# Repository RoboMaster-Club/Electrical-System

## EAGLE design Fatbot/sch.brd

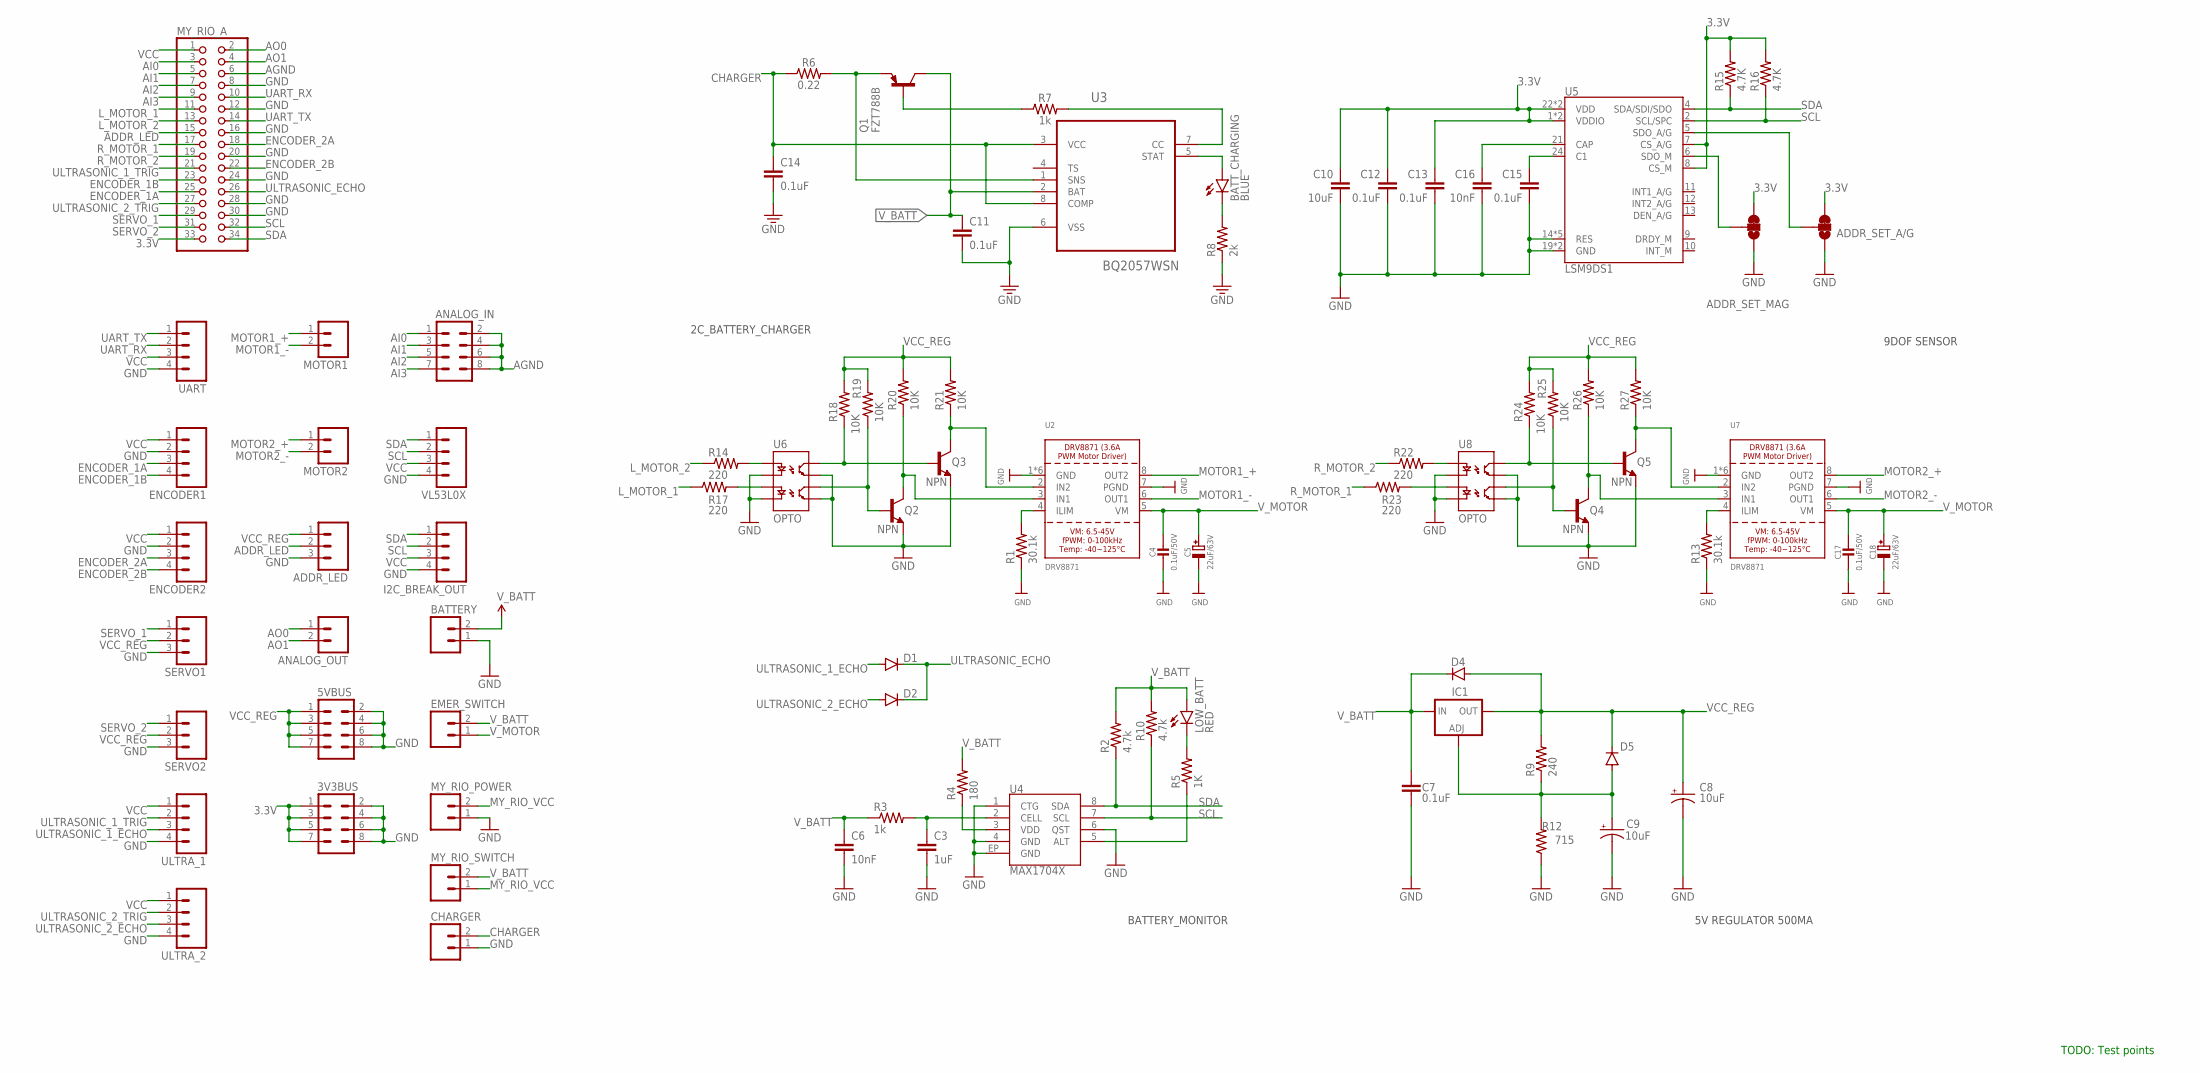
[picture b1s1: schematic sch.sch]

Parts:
3V3BUS, 5VBUS: M04X2; 2X4
ADDR_LED: M03POLAR; MOLEX-1X3
ADDR_SET_A/G: JUMPER-PAD-3-2OF3_NC_BY_TRACE_SMALL; PAD-JUMPER-3-2OF3_NC_BY_TRACE_YES_SILK_FULL_BOX
ADDR_SET_MAG: JUMPER-PAD-3-2OF3_NC_BY_TRACE_SMALL; PAD-JUMPER-3-2OF3_NC_BY_TRACE_YES_SILK_FULL_BOX
ANALOG_IN: M04X2; 2X4
ANALOG_OUT: M021X02_NO_SILK; 1X02_NO_SILK@1
BATTERY: CONN_02; 1X02
BATT_CHARGING: BLUE; LED-0603
C3: 1uF; 0402-CAP
C4, C17: 0.1uF/50V; 0805-NO
C5, C18: 22uF/63V; PANASONIC_D
C6: 10nF; 0402-CAP
C7, C12, C13, C15: 0.1uF; 0603-CAP
C8, C9: 10uF; EIA3216
C10: 10uF; 0603-CAP
C11, C14: 0.1uF; 0603
C16: 10nF; 0603-CAP
CHARGER: CONN_02; 1X02
D1, D2: DIODESOD123; SOD-123
D4, D5: 1N4002; SOD-123
EMER_SWITCH: CONN_02; 1X02
ENCODER1, ENCODER2: M041X04_NO_SILK; 1X04_NO_SILK
I2C_BREAK_OUT: M041X04_NO_SILK; 1X04_NO_SILK
IC1: LM317MBSTT3; SOT223; PARTNUMBER LM317M
LOW_BATT: RED; LED-0603
MOTOR1, MOTOR2: M02PTH; 1X02@1
MY_RIO_A: PINHD-2X17; 2X17
MY_RIO_POWER: CONN_02; 1X02
MY_RIO_SWITCH: CONN_02; 1X02
Q1: FZT788B; SOT230P700X180-4N
Q2, Q3, Q4, Q5: NPN; SOT23-3
R1, R13: 30.1k; 0603-RES
R2, R10: 4.7k; 0402-RES
R3: 1k; 0402-RES
R4: 180; 0402-RES
R5: 1K; 0603-RES
R6: 0.22; 0805@1
R7: 1k; 0603
R8: 2k; 0603-RES
R9: 240; 0603-RES
R12: 715; 0603-RES
R14, R17, R22, R23: 220; 0603-RES
R15, R16: 4.7K; 0603-RES
R18, R19, R20, R21, R24, R25, R26, R27: 10K; 0603-RES
SERVO1, SERVO2: M03POLAR; MOLEX-1X3
U2, U7: DRV8871; HSOP8
U3: BQ2057WSN; SOIC127P600X175-8N
U4: MAX1704X; TDFN-8
U5: LSM9DS1; LGA24-8X4
U6, U8: OPTO; SO08-2
UART: M04NO_SILK_ALL_ROUND; 1X04_NO_SILK_ALL_ROUND
ULTRA_1, ULTRA_2: M041X04_NO_SILK; 1X04_NO_SILK
VL53L0X: M041X04_NO_SILK; 1X04_NO_SILK

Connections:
3.3V: 3V3BUS.1, 3V3BUS.3, 3V3BUS.5, 3V3BUS.7, ADDR_SET_A/G.3, ADDR_SET_MAG.3, C10.1, C12.1, C13.1, MY_RIO_A.33, R15.2, R16.2, U5.1 (VDDIO), U5.3 (VDDIO), U5.7 (CS_A/G), U5.8 (CS_M), U5.22 (VDD), U5.23 (VDD)
ADDR_LED: ADDR_LED.2, MY_RIO_A.15
AGND: ANALOG_IN.2, ANALOG_IN.4, ANALOG_IN.6, ANALOG_IN.8, MY_RIO_A.6
AI0: ANALOG_IN.1, MY_RIO_A.3
AI1: ANALOG_IN.3, MY_RIO_A.5
AI2: ANALOG_IN.5, MY_RIO_A.7
AI3: ANALOG_IN.7, MY_RIO_A.9
ALT: R5.1, U4.5 (ALT)
AO0: ANALOG_OUT.1, MY_RIO_A.2
AO1: ANALOG_OUT.2, MY_RIO_A.4
BATTERY_MONITOR_2: BATT_CHARGING.A, U3.5 (STAT)
CHARGER: C14.1, CHARGER.2, R6.1, U3.3 (VCC), U3.8 (COMP)
ENCODER_1A: ENCODER1.3, MY_RIO_A.25
ENCODER_1B: ENCODER1.4, MY_RIO_A.23
ENCODER_2A: ENCODER2.3, MY_RIO_A.18
ENCODER_2B: ENCODER2.4, MY_RIO_A.22
GND: 3V3BUS.2, 3V3BUS.4, 3V3BUS.6, 3V3BUS.8, 5VBUS.2, 5VBUS.4, 5VBUS.6, 5VBUS.8, ADDR_LED.3, ADDR_SET_A/G.1, ADDR_SET_MAG.1, BATTERY.1, C3.2, C4.2, C5.-, C6.2, C7.2, C8.C (-), C9.C (-), C10.2, C11.2, C12.2, C13.2, C14.2, C15.2, C16.2, C17.2, C18.-, CHARGER.1, ENCODER1.2, ENCODER2.2, I2C_BREAK_OUT.4, MY_RIO_A.8, MY_RIO_A.12, MY_RIO_A.16, MY_RIO_A.20, MY_RIO_A.24, MY_RIO_A.28, MY_RIO_A.30, MY_RIO_POWER.1, Q2.2 (E), Q3.2 (E), Q4.2 (E), Q5.2 (E), R1.1, R8.1, R12.1, R13.1, SERVO1.3, SERVO2.3, U2.1 (GND), U2.7 (PGND), U2.GND, U2.P$1 (GND), U2.P$2 (GND), U2.P$3 (GND), U2.P$4 (GND), U3.6 (VSS), U4.1 (CTG), U4.4 (GND), U4.6 (QST), U4.EP (GND), U5.14 (RES), U5.15 (RES), U5.16 (RES), U5.17 (RES), U5.18 (RES), U5.19 (GND), U5.20 (GND), U6.2 (C1), U6.4 (C2), U6.5 (EM2), U6.7 (EM1), U7.1 (GND), U7.7 (PGND), U7.GND, U7.P$1 (GND), U7.P$2 (GND), U7.P$3 (GND), U7.P$4 (GND), U8.2 (C1), U8.4 (C2), U8.5 (EM2), U8.7 (EM1), UART.4, ULTRA_1.4, ULTRA_2.4, VL53L0X.4
L_MOTOR_1: MY_RIO_A.11, R17.1
L_MOTOR_2: MY_RIO_A.13, R14.1
MOTOR1_+: MOTOR1.1, U2.8 (OUT2)
MOTOR1_-: MOTOR1.2, U2.6 (OUT1)
MOTOR2_+: MOTOR2.1, U7.8 (OUT2)
MOTOR2_-: MOTOR2.2, U7.6 (OUT1)
MY_RIO_VCC: MY_RIO_POWER.2, MY_RIO_SWITCH.1
unnamed: R1.2, U2.4 (ILIM)
unnamed: R17.2, U6.3 (A2)
unnamed: C3.1, R3.2, U4.2 (CELL)
unnamed: R14.2, U6.1 (A1)
unnamed: LOW_BATT.C, R5.2
unnamed: C9.A (+), D5.A, IC1.1 (ADJ), R9.1, R12.2
unnamed: R13.2, U7.4 (ILIM)
unnamed: C16.1, U5.21 (CAP)
unnamed: C15.1, U5.24 (C1)
unnamed: R22.2, U8.1 (A1)
unnamed: R23.2, U8.3 (A2)
unnamed: Q1.3 (E), R6.2, U3.1 (SNS)
unnamed: Q1.1 (B), R7.1
unnamed: R7.2, U3.7 (CC)
unnamed: BATT_CHARGING.C, R8.2
OUT1: Q3.3 (C), R21.1, U2.2 (IN2)
OUT1N: Q3.1 (B), R18.1, U6.8 (CL1)
OUT1N1: Q5.1 (B), R24.1, U8.8 (CL1)
OUT2: Q2.3 (C), R20.1, U2.3 (IN1)
OUT2N: Q2.1 (B), R19.1, U6.6 (CL2)
OUT2N1: Q4.1 (B), R25.1, U8.6 (CL2)
OUT3: Q5.3 (C), R27.1, U7.2 (IN2)
OUT4: Q4.3 (C), R26.1, U7.3 (IN1)
R_MOTOR_1: MY_RIO_A.17, R23.1
R_MOTOR_2: MY_RIO_A.19, R22.1
SCL: I2C_BREAK_OUT.2, MY_RIO_A.32, R10.1, R16.1, U4.7 (SCL), U5.2 (SCL/SPC), VL53L0X.2
SDA: I2C_BREAK_OUT.1, MY_RIO_A.34, R2.1, R15.1, U4.8 (SDA), U5.4 (SDA/SDI/SDO), VL53L0X.1
SDO_A/G: ADDR_SET_A/G.2, U5.5 (SDO_A/G)
SDO_M: ADDR_SET_MAG.2, U5.6 (SDO_M)
SERVO_1: MY_RIO_A.29, SERVO1.1
SERVO_2: MY_RIO_A.31, SERVO2.1
UART_RX: MY_RIO_A.10, UART.2
UART_TX: MY_RIO_A.14, UART.1
ULTRASONIC_1_ECHO: D1.A, ULTRA_1.3
ULTRASONIC_1_TRIG: MY_RIO_A.21, ULTRA_1.2
ULTRASONIC_2_ECHO: D2.A, ULTRA_2.3
ULTRASONIC_2_TRIG: MY_RIO_A.27, ULTRA_2.2
ULTRASONIC_ECHO: D1.C, D2.C, MY_RIO_A.26
VCC: ENCODER1.1, ENCODER2.1, I2C_BREAK_OUT.3, MY_RIO_A.1, UART.3, ULTRA_1.1, ULTRA_2.1, VL53L0X.3
VCC_REG: 5VBUS.1, 5VBUS.3, 5VBUS.5, 5VBUS.7, ADDR_LED.1, C8.A (+), D4.A, D5.C, IC1.4 (OUT), R9.2, R18.2, R19.2, R20.2, R21.2, R24.2, R25.2, R26.2, R27.2, SERVO1.2, SERVO2.2
VDD: R4.1, U4.3 (VDD)
V_BATT: BATTERY.2, C6.1, C7.1, C11.1, D4.C, EMER_SWITCH.2, IC1.3 (IN), LOW_BATT.A, MY_RIO_SWITCH.2, Q1.2 (C), Q1.4 (C), R2.2, R3.1, R4.2, R10.2, U3.2 (BAT)
V_MOTOR: C4.1, C5.+, C17.1, C18.+, EMER_SWITCH.1, U2.5 (VM), U7.5 (VM)

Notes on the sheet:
BATTERY_MONITOR
5V REGULATOR 500MA
9DOF SENSOR
2C_BATTERY_CHARGER
TODO: Test points

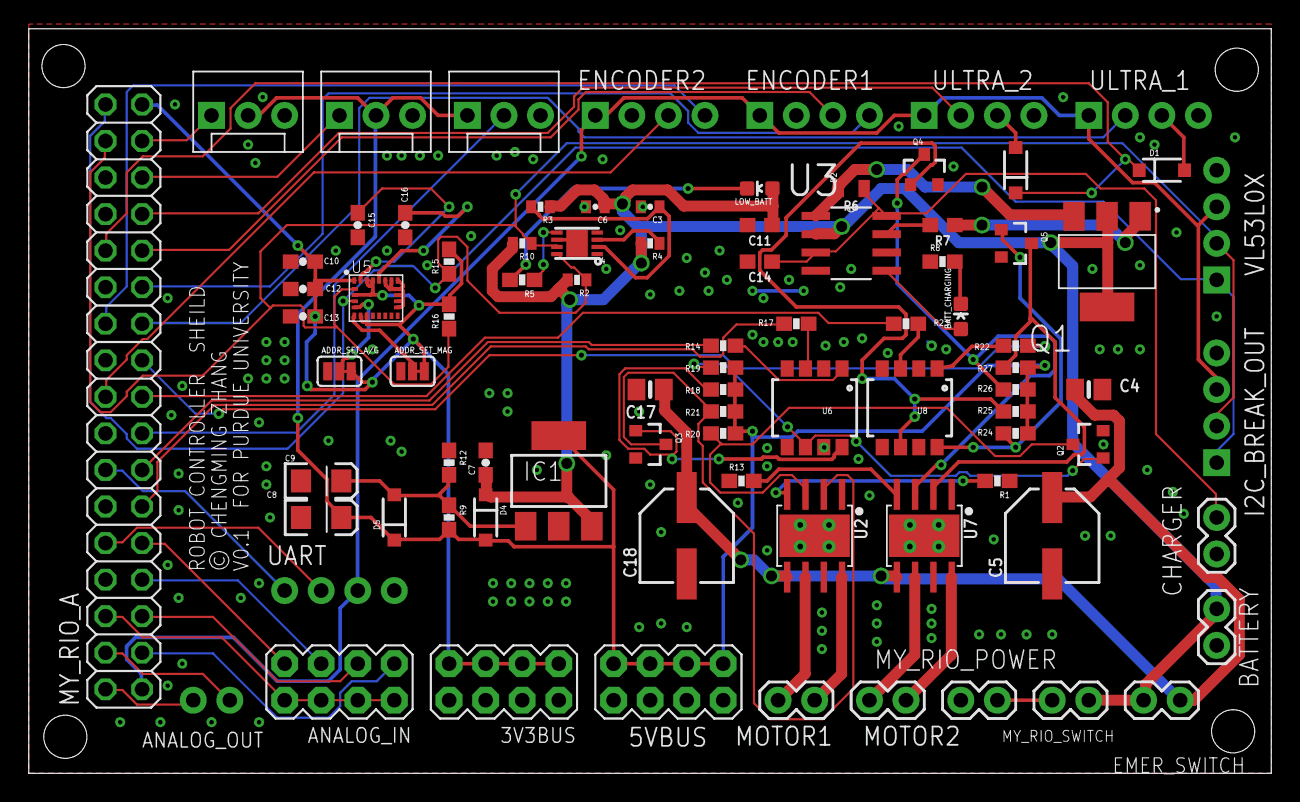
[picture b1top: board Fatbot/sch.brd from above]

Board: 2 copper layers, 86.3 x 51.7 mm, 85 parts (0 on the bottom side), 67 nets.

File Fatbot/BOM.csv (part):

"Part";"Value";"Device";"Package";"Description";"AVAILABILITY";"DESCRIPTION";"MF";"MP";"MPN";"OC_NEWARK";"PACKAGE";"PARTNUMBER";"PRICE";"PROD_ID";"VALUE";
"3V3BUS";"";"M04X2";"2X4";".1" header, two rows of four.";"";"";"";"";"";"";"";"";"";"";"";
"5VBUS";"";"M04X2";"2X4";".1" header, two rows of four.";"";"";"";"";"";"";"";"";"";"";"";
"ADDR_LED";"";"M03POLAR";"MOLEX-1X3";"Header 3";"";"";"";"";"";"";"";"";"";"";"";
"ADDR_SET_A/G";"";"JUMPER-PAD-3-2OF3_NC_BY_TRACE_SMALL";"PAD-JUMPER-3-2OF3_NC_BY_TRACE_YES_SILK_FULL_BOX";"";"";"";"";"";"";"";"";"";"";"";"";
"ADDR_SET_MAG";"";"JUMPER-PAD-3-2OF3_NC_BY_TRACE_SMALL";"PAD-JUMPER-3-2OF3_NC_BY_TRACE_YES_SILK_FULL_BOX";"";"";"";"";"";"";"";"";"";"";"";"";
"ANALOG_IN";"";"M04X2";"2X4";".1" header, two rows of four.";"";"";"";"";"";"";"";"";"";"";"";
"ANALOG_OUT";"";"M021X02_NO_SILK";"1X02_NO_SILK@1";"Standard 2-pin 0.1" header. Use with";"";"";"";"";"";"";"";"";"";"";"";
"BATTERY";"";"CONN_02";"1X02";"Multi connection point. Often used as Generic Header-pin footprint for 0.1 inch spaced/style header connections";"";"";"";"";"";"";"";"";"";"";"";
"BATT_CHARGING";"BLUE";"LED-BLUE0603";"LED-0603";"Blue LEDs for production use";"";"";"";"";"";"unknown";"";"";"";"DIO-08575";"BLUE";
"C3";"1uF";"CAP0402-CAP";"0402-CAP";"Capacitor";"";"";"";"";"";"";"";"";"";"";"";
"C4";"0.1uF/50V";"CAP_CERAMIC0805-NOOUTLINE";"0805-NO";"Ceramic Capacitors";"";"";"";"";"";"";"";"";"";"";"";
"C5";"22uF/63V";"CAP_ELECTROLYTICPANASONIC_D";"PANASONIC_D";"Electrolytic Capacitors";"";"";"";"";"";"";"";"";"";"";"";
"C6";"10nF";"CAP0402-CAP";"0402-CAP";"Capacitor";"";"";"";"";"";"";"";"";"";"";"";
"C7";"0.1uF";"0.1UF-25V(+80/-20%)(0603)";"0603-CAP";"CAP-00810";"";"";"";"";"";"";"";"";"";"CAP-00810";"0.1uF";
"C8";"10uF";"10UF-16V-10%(TANT)";"EIA3216";"CAP-00811";"";"";"";"";"";"";"";"";"";"CAP-00811";"10uF";
"C9";"10uF";"10UF-16V-10%(TANT)";"EIA3216";"CAP-00811";"";"";"";"";"";"";"";"";"";"CAP-00811";"10uF";
"C10";"10uF";"10UF-6.3V-20%(0603)";"0603-CAP";"CAP-11015";"";"";"";"";"";"";"";"";"";"CAP-11015";"10uF";
"C11";"0.1uF";"0.1UF-0603-25V-(+80/-20%)";"0603";"0.1µF ceramic capacitors";"";"";"";"";"";"unknown";"";"";"";"CAP-00810";"0.1uF";
"C12";"0.1uF";"0.1UF-25V(+80/-20%)(0603)";"0603-CAP";"CAP-00810";"";"";"";"";"";"";"";"";"";"CAP-00810";"0.1uF";
"C13";"0.1uF";"0.1UF-25V(+80/-20%)(0603)";"0603-CAP";"CAP-00810";"";"";"";"";"";"";"";"";"";"CAP-00810";"0.1uF";
"C14";"0.1uF";"0.1UF-0603-25V-(+80/-20%)";"0603";"0.1µF ceramic capacitors";"";"";"";"";"";"unknown";"";"";"";"CAP-00810";"0.1uF";
"C15";"0.1uF";"0.1UF-25V(+80/-20%)(0603)";"0603-CAP";"CAP-00810";"";"";"";"";"";"";"";"";"";"CAP-00810";"0.1uF";
"C16";"10nF";"10NF/10000PF-50V-10%(0603)";"0603-CAP";"CAP-00867";"";"";"";"";"";"";"";"";"";"CAP-00867";"10nF";
"C17";"0.1uF/50V";"CAP_CERAMIC0805-NOOUTLINE";"0805-NO";"Ceramic Capacitors";"";"";"";"";"";"";"";"";"";"";"";
"C18";"22uF/63V";"CAP_ELECTROLYTICPANASONIC_D";"PANASONIC_D";"Electrolytic Capacitors";"";"";"";"";"";"";"";"";"";"";"";
"CHARGER";"";"CONN_02";"1X02";"Multi connection point. Often used as Generic Header-pin footprint for 0.1 inch spaced/style header connections";"";"";"";"";"";"";"";"";"";"";"";
"D1";"";"DIODESOD123";"SOD-123";"Diode";"";"";"";"";"";"";"";"";"";"";"";
"D2";"";"DIODESOD123";"SOD-123";"Diode";"";"";"";"";"";"";"";"";"";"";"";
"D4";"1N4002";"DIODESOD123";"SOD-123";"Diode";"";"";"";"";"";"";"";"";"";"";"";
"D5";"1N4002";"DIODESOD123";"SOD-123";"Diode";"";"";"";"";"";"";"";"";"";"";"";
"EMER_SWITCH";"";"CONN_02";"1X02";"Multi connection point. Often used as Generic Header-pin footprint for 0.1 inch spaced/style header connections";"";"";"";"";"";"";"";"";"";"";"";
"ENCODER1";"";"M041X04_NO_SILK";"1X04_NO_SILK";"Header 4";"";"";"";"";"";"";"";"";"";"";"";
"ENCODER2";"";"M041X04_NO_SILK";"1X04_NO_SILK";"Header 4";"";"";"";"";"";"";"";"";"";"";"";
"I2C_BREAK_OUT";"";"M041X04_NO_SILK";"1X04_NO_SILK";"Header 4";"";"";"";"";"";"";"";"";"";"";"";
"IC1";"LM317MBSTT3";"LM317MBSTT3";"SOT223";"500 mA Adjustable Output Positive Voltage Regulator";"";"";"";"";"";"";"";"LM317M";"";"";"";
"LOW_BATT";"RED";"LED-RED0603";"LED-0603";"Assorted Red LEDs";"";"";"";"";"";"";"";"";"";"DIO-00819";"RED";
"MOTOR1";"";"M02PTH";"1X02@1";"Standard 2-pin 0.1" header. Use with";"";"";"";"";"";"";"";"";"";"";"";
"MOTOR2";"";"M02PTH";"1X02@1";"Standard 2-pin 0.1" header. Use with";"";"";"";"";"";"";"";"";"";"";"";
"MY_RIO_A";"";"PINHD-2X17";"2X17";"PIN HEADER";"";"";"";"";"";"";"";"";"";"";"";
"MY_RIO_POWER";"";"CONN_02";"1X02";"Multi connection point. Often used as Generic Header-pin footprint for 0.1 inch spaced/style header connections";"";"";"";"";"";"";"";"";"";"";"";
"MY_RIO_SWITCH";"";"CONN_02";"1X02";"Multi connection point. Often used as Generic Header-pin footprint for 0.1 inch spaced/style header connections";"";"";"";"";"";"";"";"";"";"";"";
"Q1";"FZT788B";"FZT788B";"SOT230P700X180-4N";"";"";"";"";"";"";"unknown";"";"";"";"";"";
"Q2";"NPN";"TRANSISTOR_NPNSOT23-3";"SOT23-3";"Transistor NPN";"";"";"";"";"";"";"";"";"";"";"";
"Q3";"NPN";"TRANSISTOR_NPNSOT23-3";"SOT23-3";"Transistor NPN";"";"";"";"";"";"";"";"";"";"";"";
"Q4";"NPN";"TRANSISTOR_NPNSOT23-3";"SOT23-3";"Transistor NPN";"";"";"";"";"";"";"";"";"";"";"";
"Q5";"NPN";"TRANSISTOR_NPNSOT23-3";"SOT23-3";"Transistor NPN";"";"";"";"";"";"";"";"";"";"";"";
"R1";"30.1k";"30.1KOHM1/10W1%(0603)";"0603-RES";"RES-08595";"";"";"";"";"";"";"";"";"";"RES-08595";"30.1k";
"R2";"4.7k";"RESISTOR0402-RES";"0402-RES";"Resistor";"";"";"";"";"";"";"";"";"";"";"";
"R3";"1k";"RESISTOR0402-RES";"0402-RES";"Resistor";"";"";"";"";"";"";"";"";"";"";"";
"R4";"180";"RESISTOR0402-RES";"0402-RES";"Resistor";"";"";"";"";"";"";"";"";"";"";"";
"R5";"1K";"1KOHM-1/10W-1%(0603)";"0603-RES";"RES-07856";"";"";"";"";"";"";"";"";"";"RES-07856";"1K";
"R6";"0.22";"0.22OHM-0805-1/4W-1%";"0805@1";"0.22Ω resistor";"";"";"";"";"";"unknown";"";"";"";"RES-09883";"0.22";
"R7";"1k";"1KOHM-0603-1/10W-1%";"0603";"1kΩ resistor";"";"";"";"";"";"unknown";"";"";"";"RES-07856";"1k";
"R8";"2k";"RESISTOR0603";"0603-RES";"Resistor";"";"";"";"";"";"unknown";"";"";"";"";"";
"R9";"240";"240OHM1/10W1%(0603)";"0603-RES";"RES-07849";"";"";"";"";"";"";"";"";"";"RES-07849";"240";
"R10";"4.7k";"RESISTOR0402-RES";"0402-RES";"Resistor";"";"";"";"";"";"";"";"";"";"";"";
"R12";"715";"715OHM1/10W1%(0603)";"0603-RES";"RES-07850";"";"";"";"";"";"";"";"";"";"RES-07850";"715";
"R13";"30.1k";"30.1KOHM1/10W1%(0603)";"0603-RES";"RES-08595";"";"";"";"";"";"";"";"";"";"RES-08595";"30.1k";
"R14";"220";"220OHM-1/10W-1%(0603)";"0603-RES";"RES-07861";"";"";"";"";"";"";"";"";"";"RES-07861";"220";
"R15";"4.7K";"4.7KOHM-1/10W-1%(0603)";"0603-RES";"RES-07857";"";"";"";"";"";"";"";"";"";"RES-07857";"4.7K";
"R16";"4.7K";"4.7KOHM-1/10W-1%(0603)";"0603-RES";"RES-07857";"";"";"";"";"";"";"";"";"";"RES-07857";"4.7K";
"R17";"220";"220OHM-1/10W-1%(0603)";"0603-RES";"RES-07861";"";"";"";"";"";"";"";"";"";"RES-07861";"220";
"R18";"10K";"10KOHM-1/10W-1%(0603)0603";"0603-RES";"RES-00824";"";"";"";"";"";"";"";"";"";"RES-00824";"10K";
"R19";"10K";"10KOHM-1/10W-1%(0603)0603";"0603-RES";"RES-00824";"";"";"";"";"";"";"";"";"";"RES-00824";"10K";
"R20";"10K";"10KOHM-1/10W-1%(0603)0603";"0603-RES";"RES-00824";"";"";"";"";"";"";"";"";"";"RES-00824";"10K";
"R21";"10K";"10KOHM-1/10W-1%(0603)0603";"0603-RES";"RES-00824";"";"";"";"";"";"";"";"";"";"RES-00824";"10K";
"R22";"220";"220OHM-1/10W-1%(0603)";"0603-RES";"RES-07861";"";"";"";"";"";"";"";"";"";"RES-07861";"220";
"R23";"220";"220OHM-1/10W-1%(0603)";"0603-RES";"RES-07861";"";"";"";"";"";"";"";"";"";"RES-07861";"220";
"R24";"10K";"10KOHM-1/10W-1%(0603)0603";"0603-RES";"RES-00824";"";"";"";"";"";"";"";"";"";"RES-00824";"10K";
"R25";"10K";"10KOHM-1/10W-1%(0603)0603";"0603-RES";"RES-00824";"";"";"";"";"";"";"";"";"";"RES-00824";"10K";
"R26";"10K";"10KOHM-1/10W-1%(0603)0603";"0603-RES";"RES-00824";"";"";"";"";"";"";"";"";"";"RES-00824";"10K";
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
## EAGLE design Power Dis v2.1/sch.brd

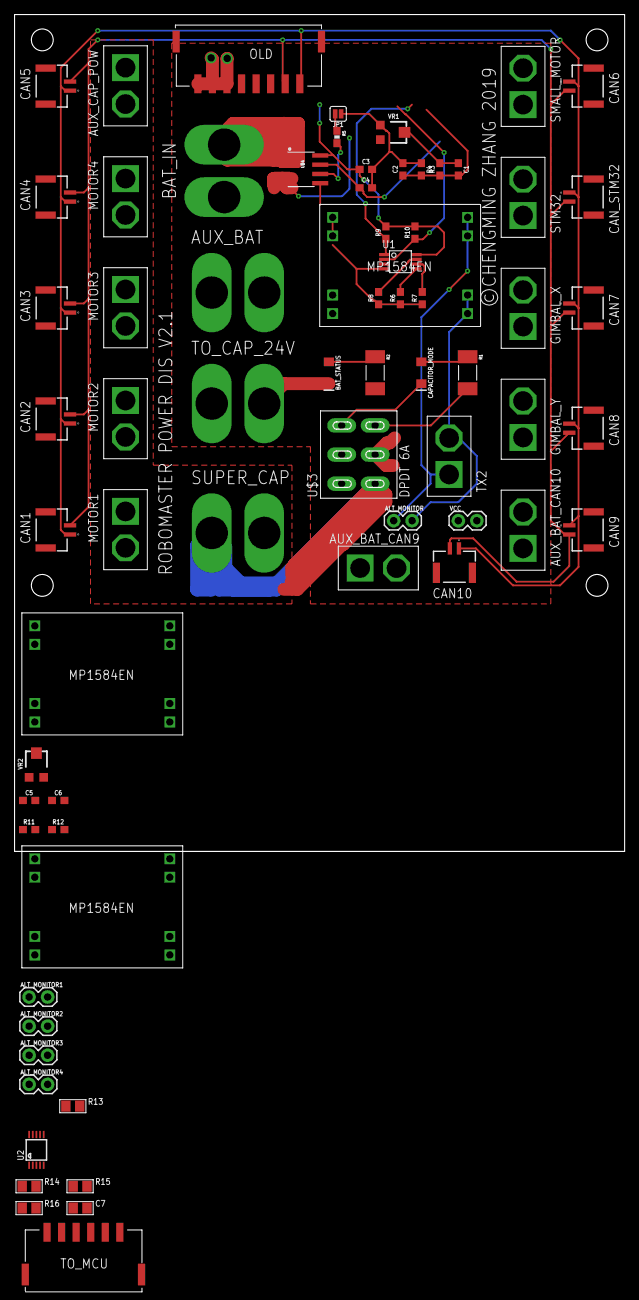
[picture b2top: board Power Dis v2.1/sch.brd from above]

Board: 2 copper layers, 83.8 x 115.0 mm, 70 parts (0 on the bottom side), 30 nets.

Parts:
ALT_MONITOR, ALT_MONITOR1, ALT_MONITOR2, ALT_MONITOR3, ALT_MONITOR4: 1X02
AUX_BAT: XT60
AUX_BAT_CAN9, AUX_BAT_CAN10: XT30
AUX_CAP_POW: XT30
BAT_IN: XT60
BAT_STATUS: 3V 20mA; LED-1206
C1, C2, C3, C5, C6: 0.1uF; 0603
C4: 1nF; 0603
C7: 1µF; 0805
CAN1, CAN2, CAN3, CAN4, CAN5, CAN6, CAN7, CAN8, CAN9, CAN10: BM02B-GHS-TBT(LF)(SN); BM02B-GHS-TBT_1
CAN_STM32: BM02B-GHS-TBT(LF)(SN); BM02B-GHS-TBT_1
CAPACITOR_MODE: 3V 20mA; LED-1206
GIMBAL_X: XT30
GIMBAL_Y: XT30
JP1: JUMPER-SMT_2_NO_SILK; SMT-JUMPER_2_NO_SILK
MOTOR1, MOTOR2, MOTOR3, MOTOR4: XT30
OLD: S8B-PH-SM4_TB
R1, R2: 1.2K; R2010
R3, R6, R7, R8, R9, R10, R11: 10k; 0603
R4, R12: 2.0k; 0603
R5: 4.7K; 0603-RES
R13, R14, R15, R16: 10K; 0805
SMALL_MOTOR: XT30
STM32: XT30
SUPER_CAP: XT60
TO_CAP_24V: XT60
TO_MCU: S6B-PH-SM4_TB
TX2: XT30
U1: MCP9808MSOP; MSOP-8
U2: ADS1115IDGST; MSOP10
U$1, U$2, U$5: MP1584; MP1584_AMAZON
U$3: DPDT
U$4: ACS723; SO08
VCC: 1X02
VR1, VR2: 10k; TRIMPOT-SMD-TC33X

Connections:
5V_AUX: ALT_MONITOR1.1, ALT_MONITOR2.1, ALT_MONITOR3.1, ALT_MONITOR4.1, U$5.7, U$5.8
ADDR: R15.1, U2.1
ALERT: R16.2, U2.2
ALT_GND: ALT_MONITOR.1, TX2.P$1, U$2.5, U$2.6
ALT_VCC: ALT_MONITOR.2, TX2.P$2, U$2.7, U$2.8
ANALOG_OUT: C1.2, C2.1, R3.1, R4.2, U2.5
BAT_24V: AUX_BAT.1, AUX_BAT_CAN9.P$2, AUX_BAT_CAN10.P$2, GIMBAL_X.P$2, GIMBAL_Y.P$2, OLD.3, OLD.4, OLD.5, R2.2, SMALL_MOTOR.P$2, STM32.P$2, TO_CAP_24V.1, U$1.3, U$1.4, U$2.3, U$2.4, U$3.P$2, U$4.3, U$4.4, U$5.3, U$5.4, VCC.2, VR1.3
BAT_GND: ALT_MONITOR1.2, ALT_MONITOR2.2, ALT_MONITOR3.2, ALT_MONITOR4.2, AUX_BAT.2, AUX_BAT_CAN9.P$1, AUX_BAT_CAN10.P$1, AUX_CAP_POW.P$1, BAT_IN.2, BAT_STATUS.C, C2.2, C3.2, C4.2, C6.2, GIMBAL_X.P$1, GIMBAL_Y.P$1, JP1.1, MOTOR1.P$1, MOTOR2.P$1, MOTOR3.P$1, MOTOR4.P$1, OLD.6, OLD.7, OLD.8, R4.1, R6.1, R7.1, R8.1, R12.1, SMALL_MOTOR.P$1, STM32.P$1, SUPER_CAP.2, TO_CAP_24V.2, TO_MCU.4, U1.4, U$1.1, U$1.2, U$1.5, U$1.6, U$2.1, U$2.2, U$3.P$4, U$3.P$5, U$4.5, U$5.1, U$5.2, U$5.5, U$5.6, VCC.1, VR1.1, VR2.1
BAT_IN: BAT_IN.1, U$4.1, U$4.2
BW_SEL: R5.2, U$4.6
CANH: CAN1.2, CAN2.2, CAN3.2, CAN4.2, CAN5.2, CAN6.2, CAN7.2, CAN8.2, CAN9.2, CAN10.2, CAN_STM32.2, OLD.2
CANL: CAN1.1, CAN2.1, CAN3.1, CAN4.1, CAN5.1, CAN6.1, CAN7.1, CAN8.1, CAN9.1, CAN10.1, CAN_STM32.1, OLD.1
CAP_24V: AUX_CAP_POW.P$2, MOTOR1.P$2, MOTOR2.P$2, MOTOR3.P$2, MOTOR4.P$2, SUPER_CAP.1, U$3.P$1, VR2.3
CAP_ANALOG_OUT: C5.2, C6.1, R11.1, R12.2, U2.6
GND: C7.1, R15.2, U2.3
MCU_VCC: C3.1, C7.2, R9.2, R10.2, R13.1, R14.1, R16.1, TO_MCU.1, U1.8, U2.8, U$1.7, U$1.8, U$4.8
unnamed: R1.2, U$3.P$3
unnamed: CAPACITOR_MODE.A, R1.1
unnamed: CAPACITOR_MODE.C, U$3.P$6
unnamed: JP1.2, R5.1
unnamed: BAT_STATUS.A, R2.1
unnamed: C5.1, R11.2, VR2.2
unnamed: TO_MCU.GND, TO_MCU.GND2
unnamed: C1.1, R3.2, VR1.2
unnamed: R8.2, U1.7
unnamed: R7.2, U1.6
unnamed: R6.2, U1.5
SCL: R10.1, R13.2, TO_MCU.3, U1.2, U2.10
SDA: R9.1, R14.2, TO_MCU.2, U1.1, U2.9
VIOUT: C4.1, U2.4, U$4.7

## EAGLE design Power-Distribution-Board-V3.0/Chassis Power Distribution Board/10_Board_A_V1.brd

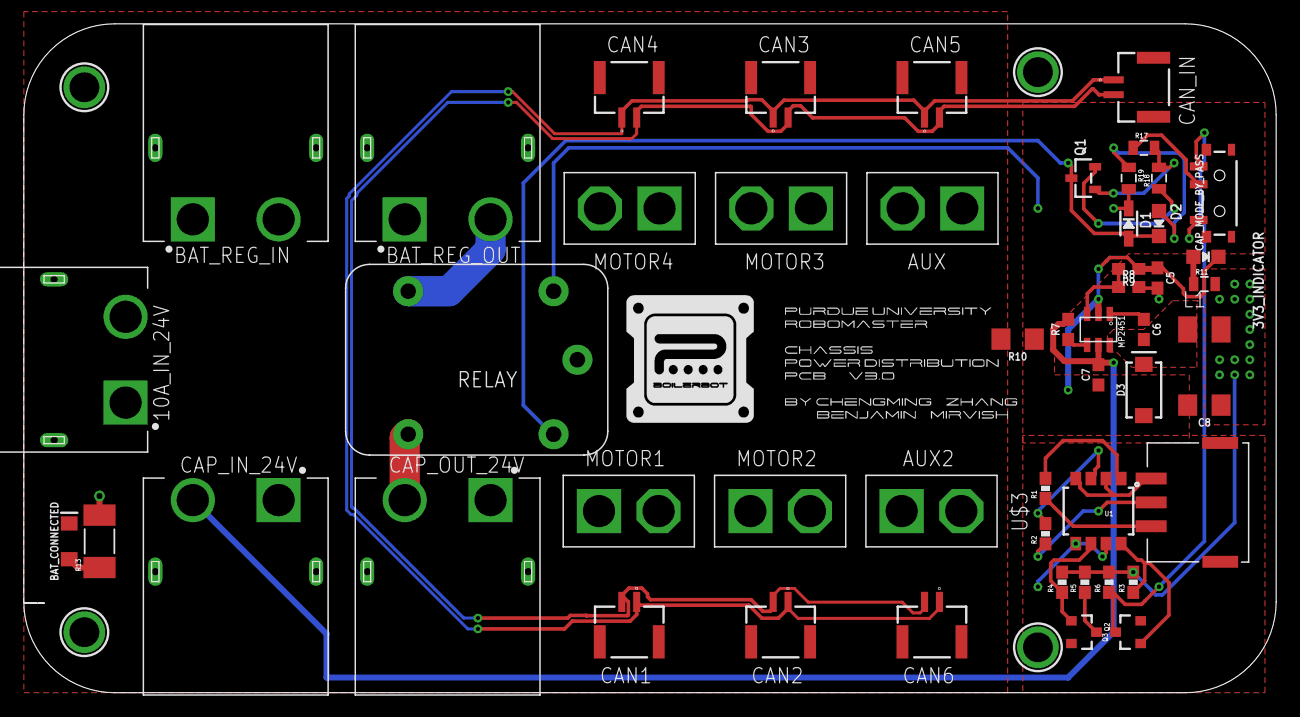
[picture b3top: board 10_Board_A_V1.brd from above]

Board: 2 copper layers, 105.1 x 56.1 mm, 55 parts (0 on the bottom side), 28 nets.

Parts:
3V3_INDICATOR: CHIPLED_0805_NOOUTLINE
10A_IN_24V: XT60PW-M; AMASS_XT60PW-M
AUX, AUX2: XT30
BAT_CONNECTED: 3V 20mA; LED-1206
BAT_REG_IN: XT60PW-M; AMASS_XT60PW-M
BAT_REG_OUT: XT60PW-M; AMASS_XT60PW-M
C5, C6, C7: 0.1uF; 0603
C8: 4.7uF; 1206
CAN1, CAN2, CAN3, CAN4, CAN5, CAN6: BM02B-GHS-TBT(LF)(SN); BM02B-GHS-TBT_1
CAN_IN: BM02B-GHS-TBT(LF)(SN); BM02B-GHS-TBT_1
CAP_IN_24V: XT60PW-M; AMASS_XT60PW-M
CAP_MODE_BY_PASS: SWITCH_SPST_SMD_A
CAP_OUT_24V: XT60PW-M; AMASS_XT60PW-M
D1: 1N4148; SOD-323
D2: CAP_INDICATOR; CHIPLED_0805_NOOUTLINE
D3: 3A/40V/500mV; SMA-DIODE
L1: SWPA3012S4R7MT; L3230M
MOTOR1, MOTOR2, MOTOR3, MOTOR4: XT30
MP2451: MP2451; TSOT-23-6-SOT-23-6
Q1: MMBT2222; SOT23-R
Q2, Q3: NPN; SOT23-3
R1, R2: 220; 0603-RES
R3, R4, R5: 10K; 0603-RES
R6: 100; 0603-RES
R7: 100K; 0603
R8: 124K; 0603
R9: 40.2k; 0603
R10: 0; 1206
R11, R17, R19: 1K; 0805
R13: 1.2K; R2010
R18: 10K; 0805
RELAY: RELAY_G5LE; RELAY_G5LE-1
U1: OPTOISOLATOR-2SOIC8; SO08-2
U$1, U$2, U$4, U$49: MOUNTINGHOLE2.5; MOUNTINGHOLE_2.5_PLATED
U$3: S3B-PH-SM4_TB

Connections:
3V3_FB: MP2451.PIN3, R8.1, R9.2
BAT_24V: 10A_IN_24V.2, BAT_REG_IN.2, C7.2, CAP_IN_24V.2, MP2451.PIN5, R7.2, R13.2
BAT_REG_24V: BAT_REG_OUT.2, RELAY.3
CAN_N: CAN1.1, CAN2.1, CAN3.1, CAN4.1, CAN5.1, CAN6.1, CAN_IN.1
CAN_P: CAN1.2, CAN2.2, CAN3.2, CAN4.2, CAN5.2, CAN6.2, CAN_IN.2
CAP_24V: CAP_OUT_24V.2, RELAY.4
CAP_OR_REG: CAP_MODE_BY_PASS.1, Q3.3, R6.1
GND: 10A_IN_24V.1, AUX.P$1, AUX2.P$1, BAT_CONNECTED.C, BAT_REG_IN.1, BAT_REG_OUT.1, CAP_IN_24V.1, CAP_OUT_24V.1, MOTOR1.P$1, MOTOR2.P$1, MOTOR3.P$1, MOTOR4.P$1, R10.2
IN1: R1.1, U$3.1
IN2: R2.1, U$3.2
LOW_GND: U1.2, U1.4, U$3.3
MOTOR_24V: AUX.P$2, AUX2.P$2, MOTOR1.P$2, MOTOR2.P$2, MOTOR3.P$2, MOTOR4.P$2, RELAY.1
unnamed: CAP_MODE_BY_PASS.2, R17.1
unnamed: R1.2, U1.1
unnamed: R2.2, U1.3
unnamed: MP2451.PIN4, R7.1
unnamed: C6.1, MP2451.PIN1
unnamed: C6.2, D3.C, L1.1, MP2451.PIN6
unnamed: 3V3_INDICATOR.A, R11.1
unnamed: BAT_CONNECTED.A, R13.1
unnamed: D1.A, D2.C, Q1.3, RELAY.5
unnamed: Q1.1, R17.2, R18.2
unnamed: D2.A, R19.1
OUT1N: Q3.1, R3.1, U1.8
OUT2: Q2.3, R5.1
OUT2N: Q2.1, R4.1, U1.6
SIG_GND: 3V3_INDICATOR.C, C5.1, C7.1, C8.2, D3.A, MP2451.PIN2, Q1.2, Q2.2, Q3.2, R9.1, R10.1, R18.1, U1.5, U1.7
VCC: C5.2, C8.1, CAP_MODE_BY_PASS.3, D1.C, L1.2, R3.2, R4.2, R5.2, R6.2, R8.2, R11.2, R19.2, RELAY.2

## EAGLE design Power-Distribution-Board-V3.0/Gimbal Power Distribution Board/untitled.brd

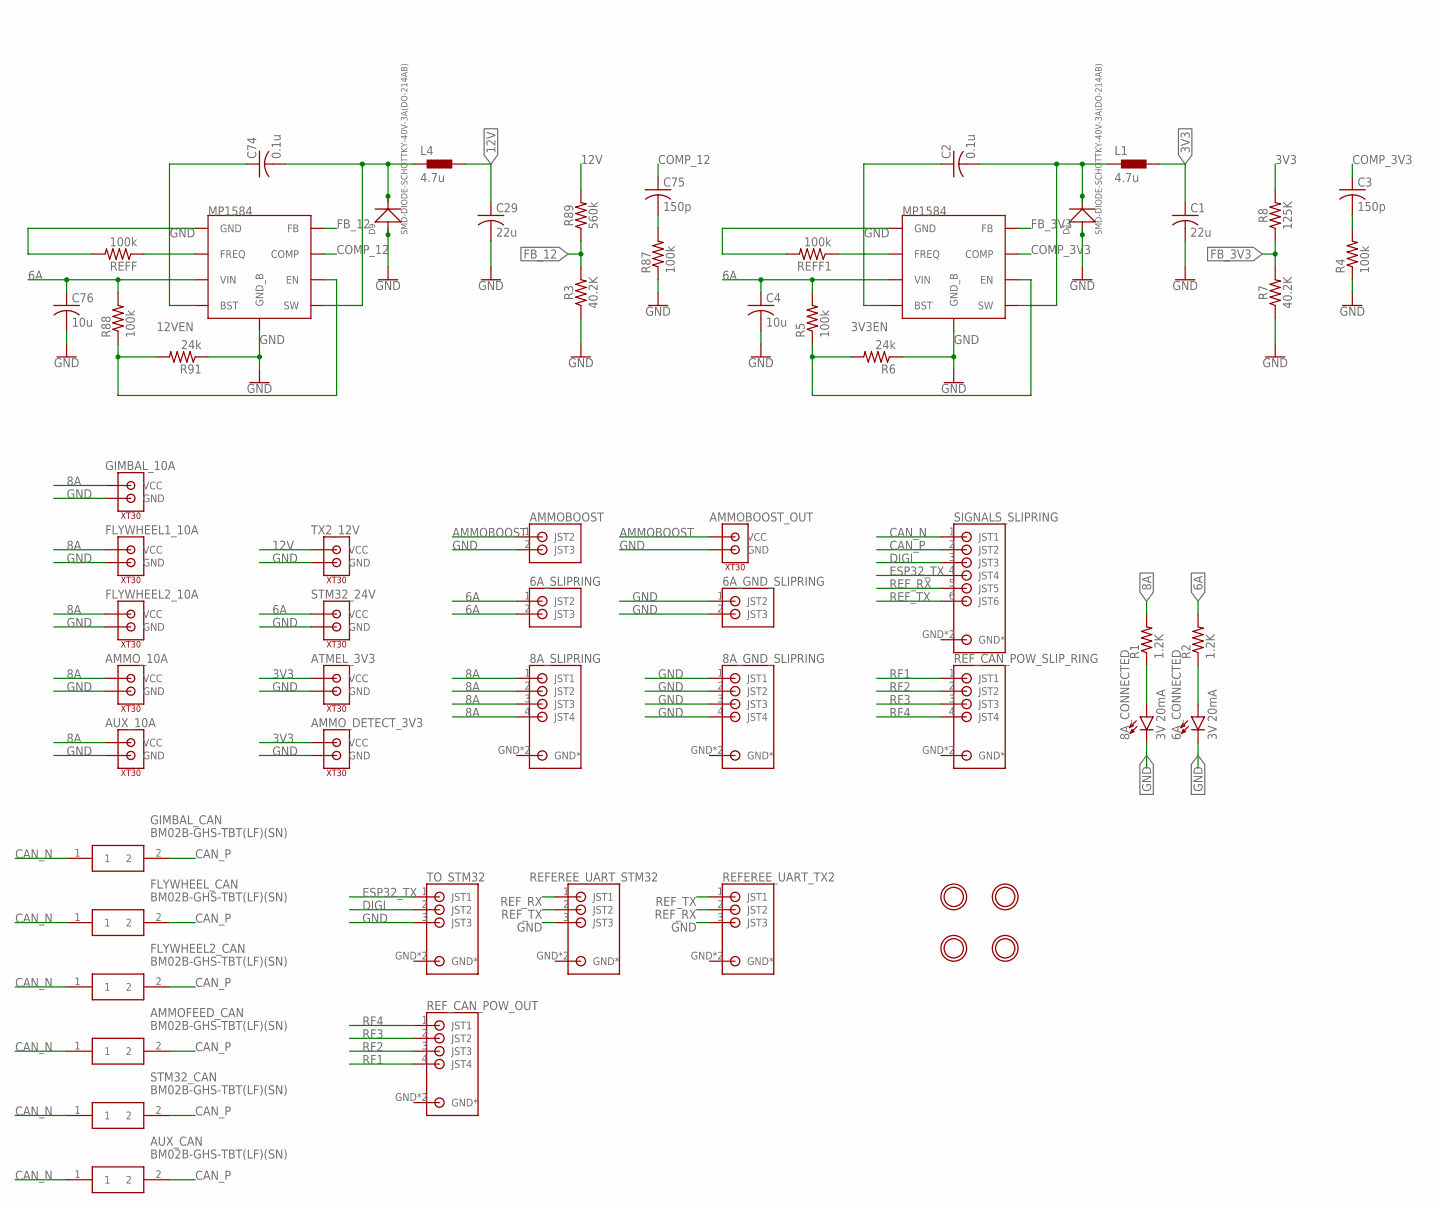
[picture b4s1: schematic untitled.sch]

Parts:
6A_CONNECTED, 8A_CONNECTED: 3V 20mA; LED-1206
6A_GND_SLIPRING, 6A_SLIPRING: S2B-PH-SM4_TB
8A_GND_SLIPRING, 8A_SLIPRING: S4B-PH-SM4_TB
AMMOBOOST: S2B-PH-SM4_TB
AMMOBOOST_OUT: XT30
AMMOFEED_CAN: BM02B-GHS-TBT(LF)(SN); BM02B-GHS-TBT_1
AMMO_10A: XT30
AMMO_DETECT_3V3: XT30
ATMEL_3V3: XT30
AUX_10A: XT30
AUX_CAN: BM02B-GHS-TBT(LF)(SN); BM02B-GHS-TBT_1
C1, C29: 22u; C1206
C2, C74: 0.1u; C0603
C3, C75: 150p; C0603
C4, C76: 10u; C1206
D1, D9: SMD-DIODE-SCHOTTKY-40V-3A(DO-214AB); DO-214AB
FLYWHEEL1_10A, FLYWHEEL2_10A: XT30
FLYWHEEL2_CAN: BM02B-GHS-TBT(LF)(SN); BM02B-GHS-TBT_1
FLYWHEEL_CAN: BM02B-GHS-TBT(LF)(SN); BM02B-GHS-TBT_1
GIMBAL_10A: XT30
GIMBAL_CAN: BM02B-GHS-TBT(LF)(SN); BM02B-GHS-TBT_1
L1, L4: 4.7u; MHCI0603-4R7M-R8
R1, R2: 1.2K; R2010
R3, R7: 40.2K; 0603
R4, R5, R87, R88: 100k; R0603
R6, R91: 24k; R0603
R8: 125K; 0603
R89: 560k; 0603
REFEREE_UART_STM32: S3B-PH-SM4_TB
REFEREE_UART_TX2: S3B-PH-SM4_TB
REFF, REFF1: 100k; R0603
REF_CAN_POW_OUT: S4B-PH-SM4_TB
REF_CAN_POW_SLIP_RING: S4B-PH-SM4_TB
SIGNALS_SLIPRING: S6B-PH-SM4_TB
STM32_24V: XT30
STM32_CAN: BM02B-GHS-TBT(LF)(SN); BM02B-GHS-TBT_1
TO_STM32: S3B-PH-SM4_TB
TX2_12V: XT30
U$1, U$2, U$4, U$49: MOUNTINGHOLE2.5; MOUNTINGHOLE_2.5_PLATED
U$3, U$5: MP1584_V2

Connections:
3V3: AMMO_DETECT_3V3.P$2 (VCC), ATMEL_3V3.P$2 (VCC), C1.1, L1.P$2 (2), R8.2
3V3EN: R5.1, R6.2, U$5.EN
6A: 6A_SLIPRING.1 (JST2), 6A_SLIPRING.2 (JST3), C4.1, C76.1, R2.2, R5.2, R88.2, STM32_24V.P$2 (VCC), U$3.VIN, U$5.VIN
8A: 8A_SLIPRING.1 (JST1), 8A_SLIPRING.2 (JST2), 8A_SLIPRING.3 (JST3), 8A_SLIPRING.4 (JST4), AMMO_10A.P$2 (VCC), AUX_10A.P$2 (VCC), FLYWHEEL1_10A.P$2 (VCC), FLYWHEEL2_10A.P$2 (VCC), GIMBAL_10A.P$2 (VCC), R1.2
12V: C29.1, L4.P$2 (2), R89.2, TX2_12V.P$2 (VCC)
12VEN: R88.1, R91.2, U$3.EN
AMMOBOOST: AMMOBOOST.1 (JST2), AMMOBOOST_OUT.P$2 (VCC)
BST: C74.1, U$3.BST
BST1: C2.1, U$5.BST
CAN_N: AMMOFEED_CAN.1, AUX_CAN.1, FLYWHEEL2_CAN.1, FLYWHEEL_CAN.1, GIMBAL_CAN.1, SIGNALS_SLIPRING.1 (JST1), STM32_CAN.1
CAN_P: AMMOFEED_CAN.2, AUX_CAN.2, FLYWHEEL2_CAN.2, FLYWHEEL_CAN.2, GIMBAL_CAN.2, SIGNALS_SLIPRING.2 (JST2), STM32_CAN.2
COMP_3V3: C3.1, U$5.COMP
COMP_12: C75.1, U$3.COMP
DIGI: SIGNALS_SLIPRING.3 (JST3), TO_STM32.2 (JST2)
ESP32_TX: SIGNALS_SLIPRING.4 (JST4), TO_STM32.1 (JST1)
FB_3V3: R7.2, R8.1, U$5.FB
FB_12: R3.2, R89.1, U$3.FB
FREQ: REFF.1, U$3.FREQ
FREQ1: REFF1.1, U$5.FREQ
GND: 6A_CONNECTED.C, 6A_GND_SLIPRING.1 (JST2), 6A_GND_SLIPRING.2 (JST3), 8A_CONNECTED.C, 8A_GND_SLIPRING.1 (JST1), 8A_GND_SLIPRING.2 (JST2), 8A_GND_SLIPRING.3 (JST3), 8A_GND_SLIPRING.4 (JST4), AMMOBOOST.2 (JST3), AMMOBOOST_OUT.P$1 (GND), AMMO_10A.P$1 (GND), AMMO_DETECT_3V3.P$1 (GND), ATMEL_3V3.P$1 (GND), AUX_10A.P$1 (GND), C1.2, C4.2, C29.2, C76.2, D1.1 (+), D9.1 (+), FLYWHEEL1_10A.P$1 (GND), FLYWHEEL2_10A.P$1 (GND), GIMBAL_10A.P$1 (GND), R3.1, R4.1, R6.1, R7.1, R87.1, R91.1, REFEREE_UART_STM32.3 (JST3), REFEREE_UART_TX2.3 (JST3), REFF.2, REFF1.2, STM32_24V.P$1 (GND), TO_STM32.3 (JST3), TX2_12V.P$1 (GND), U$3.GND, U$3.GND_B, U$5.GND, U$5.GND_B
unnamed: 6A_CONNECTED.A, R2.1
unnamed: 8A_CONNECTED.A, R1.1
unnamed: C3.2, R4.2
unnamed: C75.2, R87.2
REF_RX: REFEREE_UART_STM32.1 (JST1), REFEREE_UART_TX2.2 (JST2), SIGNALS_SLIPRING.5 (JST5)
REF_TX: REFEREE_UART_STM32.2 (JST2), REFEREE_UART_TX2.1 (JST1), SIGNALS_SLIPRING.6 (JST6)
RF1: REF_CAN_POW_OUT.4 (JST4), REF_CAN_POW_SLIP_RING.1 (JST1)
RF2: REF_CAN_POW_OUT.3 (JST3), REF_CAN_POW_SLIP_RING.2 (JST2)
RF3: REF_CAN_POW_OUT.2 (JST2), REF_CAN_POW_SLIP_RING.3 (JST3)
RF4: REF_CAN_POW_OUT.1 (JST1), REF_CAN_POW_SLIP_RING.4 (JST4)
SW: C74.2, D9.2 (-), L4.P$1 (1), U$3.SW
SW1: C2.2, D1.2 (-), L1.P$1 (1), U$5.SW

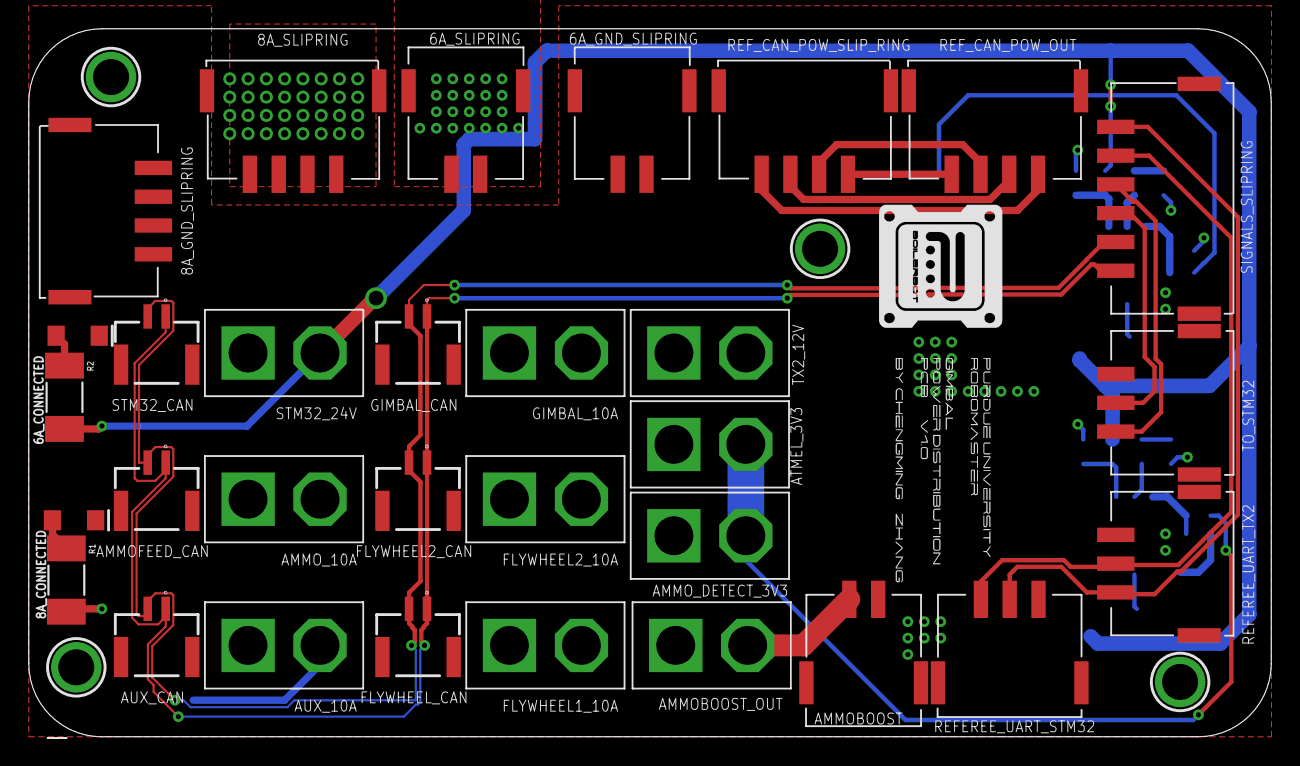
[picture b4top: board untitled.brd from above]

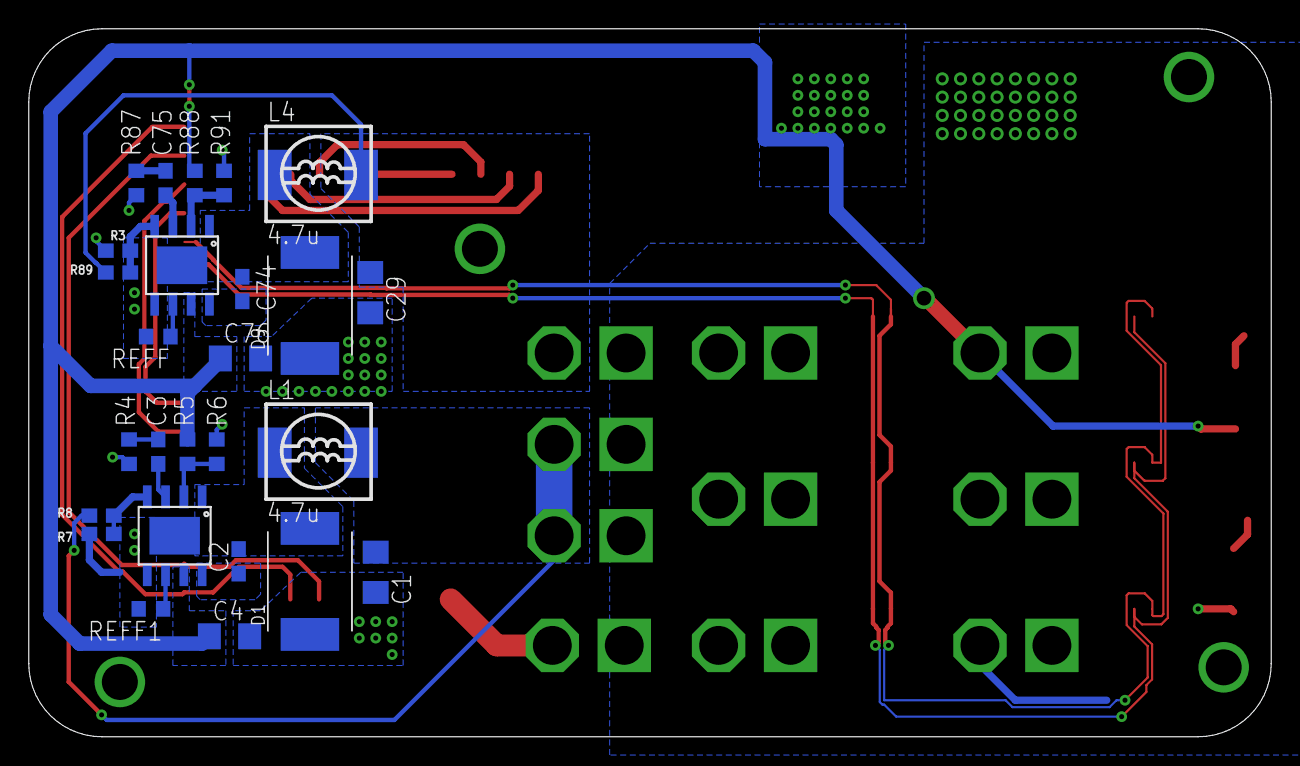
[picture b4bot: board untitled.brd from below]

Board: 2 copper layers, 86.3 x 49.2 mm, 61 parts (26 on the bottom side), 32 nets.

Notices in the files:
Fatbot/sch.brd:
© CHENGMING ZHANG
Power Dis v2.1/sch.brd:
©CHENGMING ZHANG 2019
parts and their libraries:
SparkFun-Connectors: Licensing: Creative Commons ShareAlike 4.0 International - https://creativecommons.org/licenses/by-sa/4.0
microbuilder: This work is placed in the public domain, and may be freely used for commercial and non-commercial work with the following conditions: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
